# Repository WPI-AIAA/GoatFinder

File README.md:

# Goat Finder
### Worcester Polytechnic Institute AIAA
### Battle of the Rockets 2018

## Adding the Repository
Clone the repository to a directory
```
$~ git clone https://github.com/WPI-AIAA/GoatFinder
$~ git checkout dev
```

From here move into a specific branch
```
$~ git checkout <branch>
```

We will be working out of two primary branches within dev
```
groundStation
rover
```

## SSH for PI
ssh pi@BOR-pi.dyn.wpi.edu, password: see GroupMe

## Setting up the PI Zero W

### Disable BlueTooth

1. Open config.txt
   `sudo nano /boot/config.txt`

2. Add the following line to the file
   `dtoverlay=pi3-disable-bt`

3. Reboot
   `sudo reboot`

### Enabling I2C 

Taken from [Adafruit](https://learn.adafruit.com/adafruits-raspberry-pi-lesson-4-gpio-setup/configuring-i2c)

1. Install I2C tools
   `sudo apt install -y python-smbus`
   `sudo apt install -y i2c-tools`

2. Install Kernel Support
   `sudo raspi-config`

3. Navigate to Interfacing Options and Enable I2C

4. Reboot
   `sudo reboot`

5. Check for attached I2C devices
   `sudo i2cdetect -y 1`

### Enable SPI

Taken from [Adafruit](https://learn.adafruit.com/adafruits-raspberry-pi-lesson-4-gpio-setup/configuring-spi)

1. ​Remove the blacklist for the SPI module
   `sudo nano /etc/modprobe.d/rapsi-blacklist.conf`

2. Reboot
   `sudo reboot`

3. Check the devices are available
   `ls -l /dev/spidev*`

### Enable UART

1. Install Serial Library
   `sudo apt install python-serial`

### Install Django

Taken from [Django](https://docs.djangoproject.com/)

1. Install Python
   `sudo apt install python3`

2. Setup a Database (optional)
   `place holder`

3. Install PIP
   `place holder`

4. Install Django
   `place holder`

## Standards

### General GPIO

We will be using the BCM GPIO numbering
```python
import RPi.GPIO as GPIO
GPIO.setmode(GPIO.BCM)
```

### Using I2C

I2C will be used to interface with the BMP280 and LSM9DS0
```python
import smbus
myDevice = smbus.SMBus(1) # The Pi has two available busses, 0 and 1
myAddress = 0x00 # Device address

def read(byte):
	return(myDevice.read_byte_data(myAddress, byte)) # Read a Byte

def write(byte, value):
	myDevice.write_byte_data(myAddress, byte, value) # Set a Byte to Value
```

### Using UART

UART will be used to interface with the XBEE Radio or GPS
```python
import serial
port = serial.Serial("/dev/ttyAMA0", baudrate=115200, timeout=3.0) # ttyAMA0 corresponds to the UART interface

port.write("Sometext")
port.read(10) # Read 10 Characters
```

### XBEE

XBEE Radio Protocol Options
+ Ad Hoc Wireless Network Mode
+ Serial Communication Service
+ API Mode

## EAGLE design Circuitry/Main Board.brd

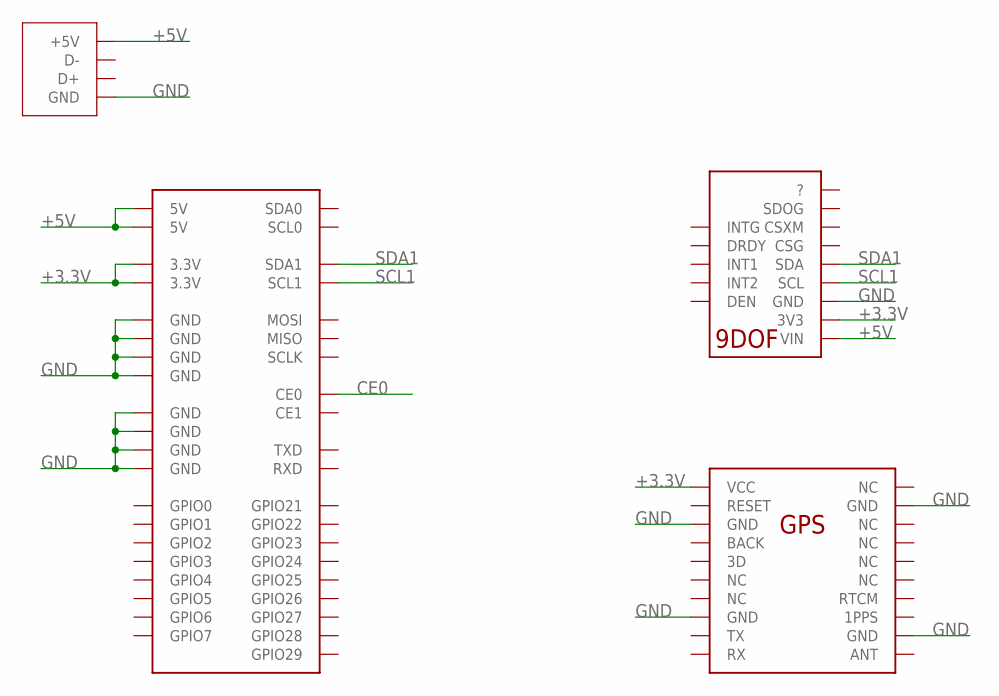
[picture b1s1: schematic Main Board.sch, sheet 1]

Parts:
U$5: GPS
U$6: 9DOF
U$8: USB_VERTICLE
U$11: PI; PI_HEADER_SMD

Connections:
+3.3V: U$5.P$1 (VCC), U$6.P$21 (3V3), U$11.3.3V@1 (3.3V), U$11.3.3V@17 (3.3V)
+5V: U$6.P$20 (VIN), U$8.VCC (+5V), U$11.5V@2 (5V), U$11.5V@4 (5V)
CE0: U$11.CE0
GND: U$5.P$3 (GND), U$5.P$8 (GND), U$5.P$12 (GND), U$5.P$19 (GND), U$6.P$22 (GND), U$8.GND@1 (GND), U$8.GND@2 (GND), U$8.GND@3 (GND), U$11.GND@6 (GND), U$11.GND@9 (GND), U$11.GND@14 (GND), U$11.GND@20 (GND), U$11.GND@25 (GND), U$11.GND@30 (GND), U$11.GND@34 (GND), U$11.GND@39 (GND)
SCL1: U$6.P$23 (SCL), U$11.SCL1
SDA1: U$6.P$24 (SDA), U$11.SDA1

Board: 2 copper layers, 4 parts (1 on the bottom side), 5 nets, no tracks yet.

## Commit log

2017-11-06 Added folders
2017-11-06 Updated README.md with setup information.
2017-11-06 Further README updates
2017-11-08 Removed PCB files
2017-11-08 got rid of XBee section
2017-11-17 Minor changes
2017-12-07 Added Camera info to ReadMe Minor ReadMe changes
2017-12-11 Updated README to have the right link for cloning the repo
2018-01-10 Functions for GPS
    Run initGPS() at the beginning, readGPS().get('latitude') and readGPS().get('longitude') to get lat and long.
    Some stuff needs to be done on the pi first, instructions here: https://learn.adafruit.com/adafruit-ultimate-gps-on-the-raspberry-pi?view=all
2018-01-18 9DOF Libiary with examples
2018-02-11 Added preliminary PID controller and drive function. function queue should be pretty much done for our needs
2018-02-12 Created a directory for all information regarding the webserver in addition to a README that explains that Apache webserver and the index.html file that needs to be changed.
2018-02-13 made it so that the drive function actually has a loop that can exit
2018-02-13 did some simulation stuff for the drive function. worked out some trig mistakes
2018-02-13 fixed angle issues causing the rover to turn in the wrong direction (ex. turning from 359* to 1* would turn CCW 358* instead of CW 2*)
2018-02-19 more work on improving the simulation
2018-02-19 Added SSH information to README
2018-02-20 initial altitude detection stuff done
2018-02-26 initial nav system commit
2018-02-27 cleaned up silly mistakes
2018-03-18 some changes to high level drive function
2018-03-25 started IO macro bit
2018-03-25 who knows which pins we're using? not this guy
2018-03-25 drive.py should work with motor output now. macro updated because of a mistake
2018-04-01 more work on IO and motors
2018-04-01 new, final-ish navSystem_hall
2018-04-01 added old function queue stuff
2018-04-01 removing simulation stuff
2018-04-01 Removed GPS file as GPS is no longer needed.
2018-04-01 This does nothing.
2018-04-01 thread framework
2018-04-01 thread framework pt 2
2018-04-04 final (hopefully) navsystem hall
2018-04-04 Moved 9DOF Sensor file to main directory
2018-04-04 drive should work now
2018-04-04 initialize nav system
2018-04-04 Added barometer class to initialize and added ability to read altitude
2018-04-04 started on threads
2018-04-04 using BCM and not BOARD naming schemes for pins
2018-04-07 added some stuff to ensure proper operation
2018-04-07 finished nav thread (hopefully), fixed syntax in navsystem
2018-04-07 removed manually set delta time for more accurate time library-based method. should improve stability in real-world usage. May need to set a sleep in the drive function though
2018-04-07 should properly address motors now. not using PWM controllers, using BCM 20 and 21 (board 38 and 40)
2018-04-08 add pinout notes
2018-04-08 servo PWM controller should be done, including motors, droppers, and parachute
2018-04-08 wrote some basic test programs for the PWM controller and motors
2018-04-08 perfboard motor control pin docs
2018-04-08 reassigning pins
2018-04-09 some pwm changes, notes for i2c
2018-04-09 please excuse
2018-04-09 testing second i2c address
2018-04-09 quick maffs
2018-04-09 asdkfkfkfkadfa
2018-04-09 im dum
2018-04-09 oops
2018-04-09 negative values are bad
2018-04-09 doing a test
2018-04-09 more tests
2018-04-09 pwm works
2018-04-09 switched to perfboard
2018-04-09 unused import
2018-04-09 switching back to pcb
2018-04-09 change to the motor output test
2018-04-09 added example nav system generator
2018-04-10 last minute things
2018-04-10 main should run...
2018-04-10 redo nav global as separate file
2018-04-10 redo nav global for drive.py
2018-04-10 fixed a LOT of syntax errors in navsystem
2018-04-10 a lot of fixes
2018-04-10 unfucked the 20 NaNs
2018-04-11 changes on the pi
2018-04-11 fuck you python fix globals
2018-04-11 it's alive, kinda
2018-04-11 updated basic mission, added specific turn function to drive
2018-04-11 added in motor stops after completion
2018-04-11 switched left and right motors. Left motor is now motor 1
2018-04-11 added servo handler. works with the parachute and the markers. might need to adjust the min and max pwms in pwmHelper.py. also might need to swap OPEN and CLOSED
2018-04-12 redo timescale to use actual time rather than estimates
2018-04-12 fixed units and used atan2 instead of atan
2018-04-12 unfucked the global sharing (only shares nav now)
2018-04-12 switched motor movement directions
2018-04-12 added in some speed checks. rover should approach the target more quickly, and shouldn't have as much difficulty turning
2018-04-12 some drive modifications or something
2018-04-12 all the stuff getting ready for the merge
2018-04-12 increased refresh rate of 9dof to 100hz
2018-04-12 changes to drive and navsystem to make driving nicer. Pushed initial scripts to manage changing the wireless to ad-hoc mode.
2018-04-13 some assorted stuff, trying to do magnetometer stuff
2018-04-13 magnetometer calibration code added
2018-04-13 re-added motor movement
2018-04-13 some more work
2018-04-13 some work for determining velocity dependence of magnetometer
2018-04-13 image stuff and some magnetometer stuff
2018-04-13 added gyro option
2018-04-13 fixed syntax in gyro nav sys
2018-04-13 add gyro zeroing
2018-04-13 add gyro zeroing for all the files
2018-04-13 fuckin filters
2018-04-13 it's so late who knows
2018-04-13 modified necessary files, added commented out main mission
2018-04-13 too much to list but weew a lot of shit works
2018-04-13 dropped that first fucking stupid sample
2018-04-14 Add file to read hall effect sensor
2018-04-14 Added the correct pins to the code
